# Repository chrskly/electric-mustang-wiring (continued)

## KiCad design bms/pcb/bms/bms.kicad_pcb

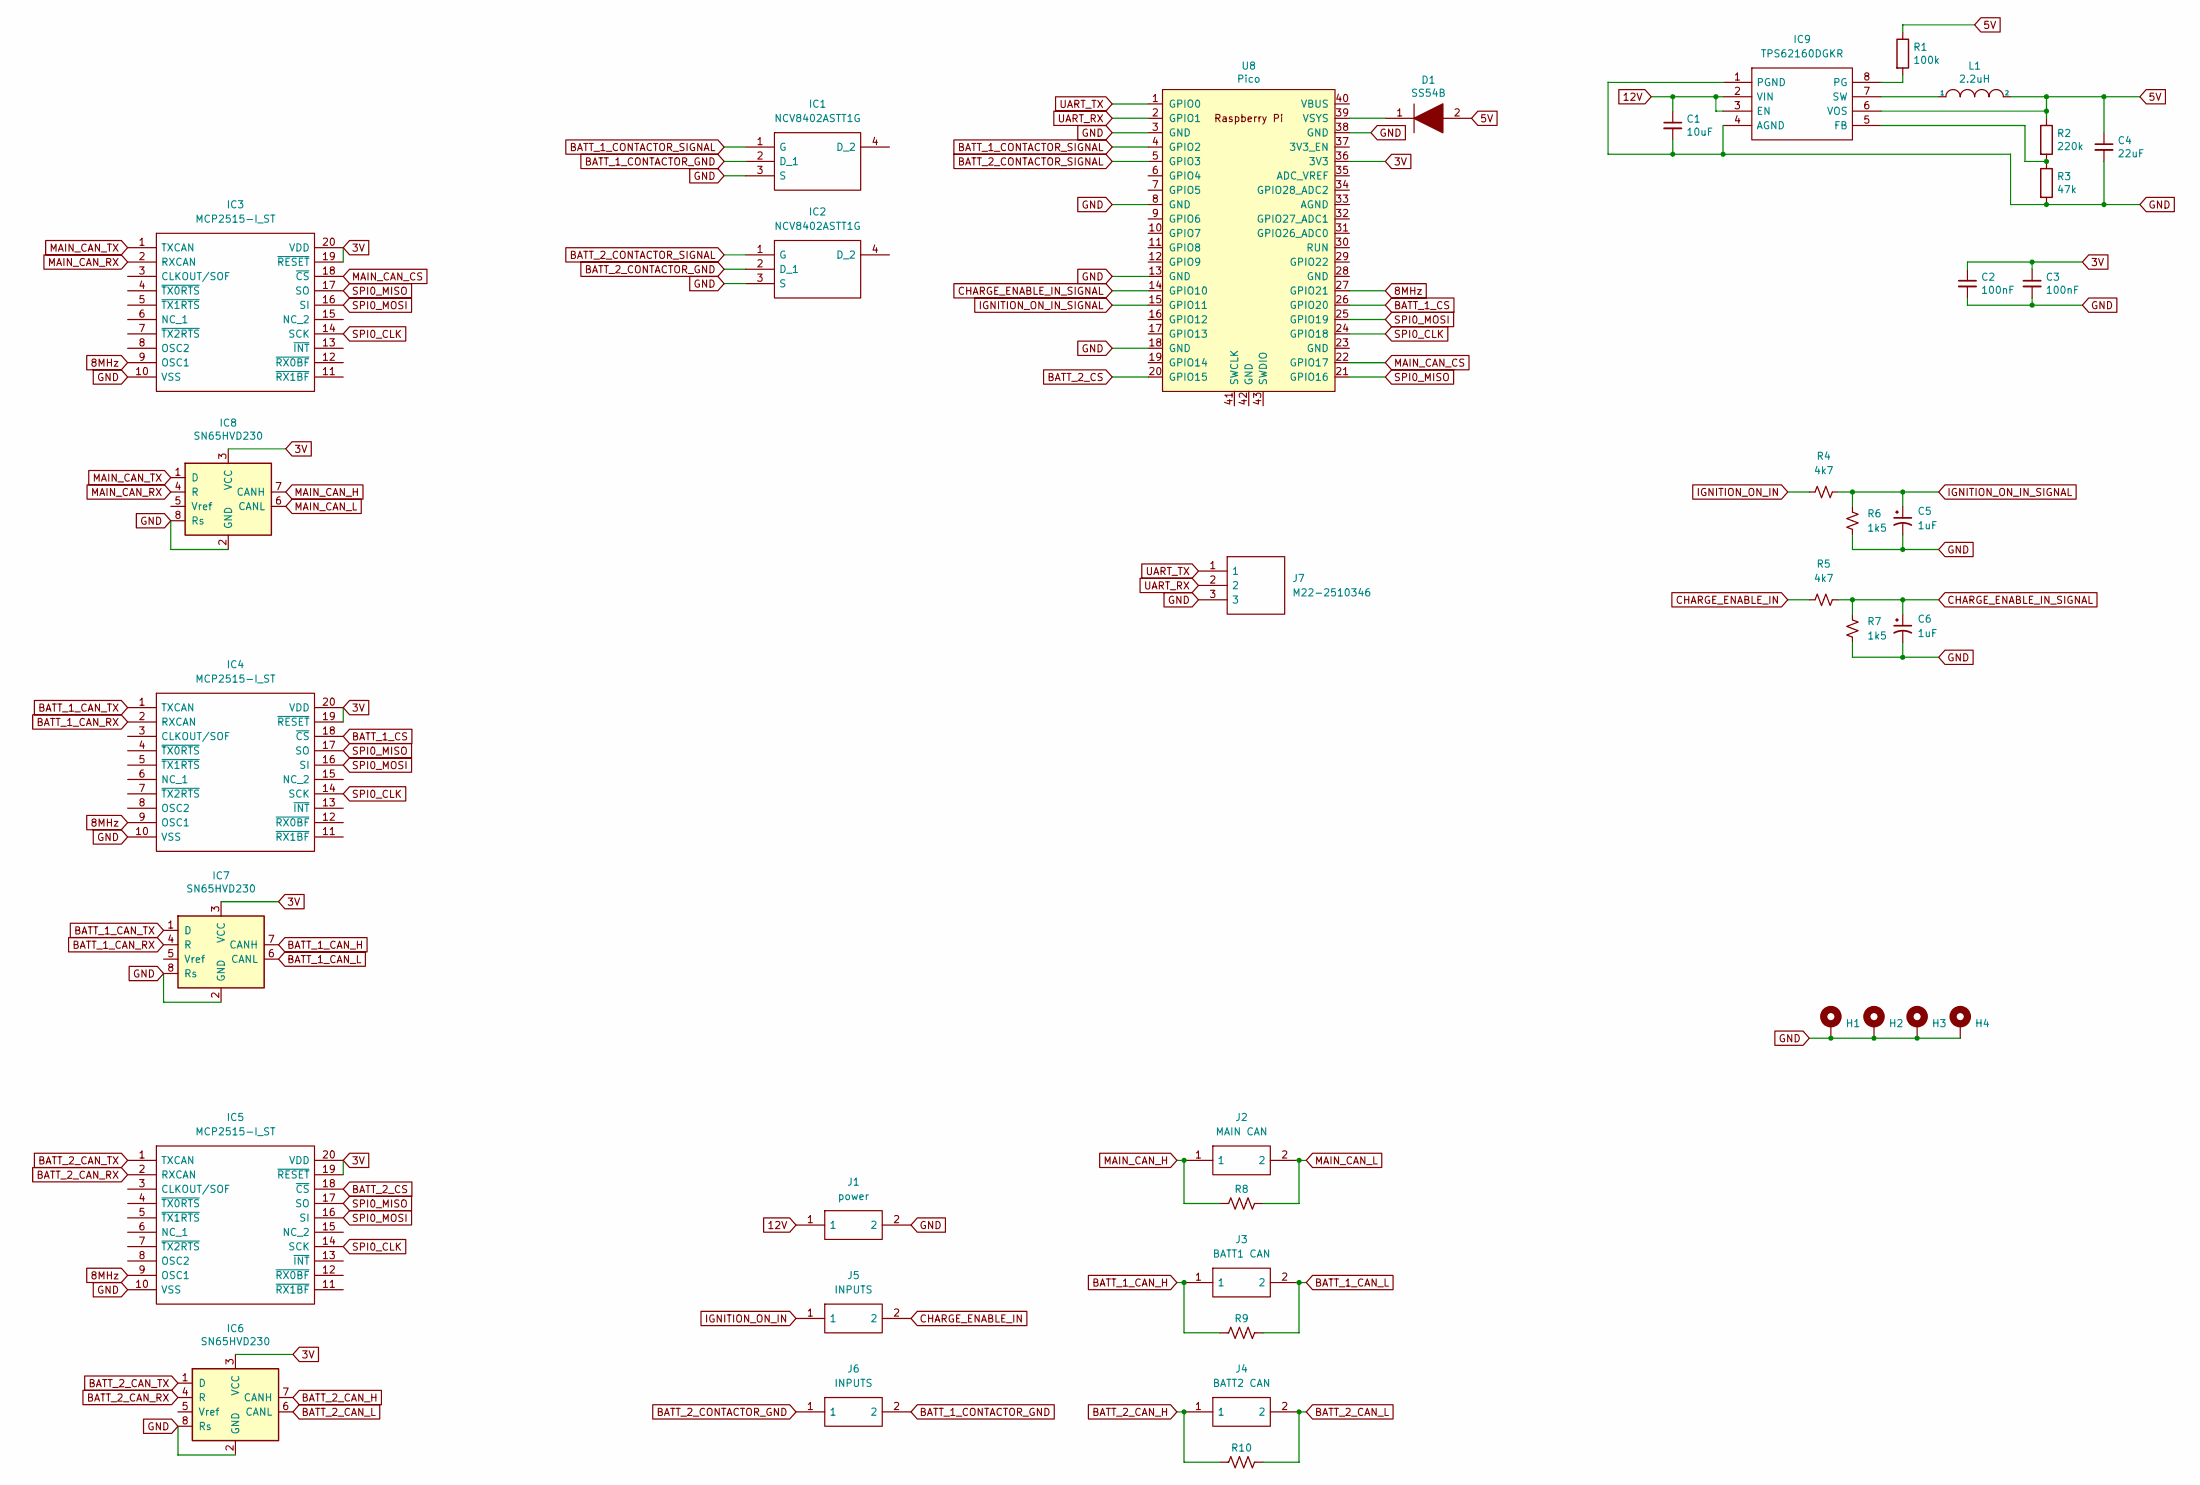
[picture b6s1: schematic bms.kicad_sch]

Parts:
C1: 10uF; C_0603_1608Metric
C2, C3: 100nF; C_0603_1608Metric
C4: 22uF; C_0805_2012Metric
C5, C6: 1uF; C_0603_1608Metric
D1: SS54B; DIOM5336X244N; Manufacturer_Part_Number SS54B
H1, H2, H3, H4: MountingHole; MountingHole_3.2mm_M3_Pad
IC1, IC2: NCV8402ASTT1G; SOT230P700X175-4N; Manufacturer_Part_Number NCV8402ASTT1G; Mouser Part Number 863-NCV8402ASTT1G
IC3, IC4, IC5: MCP2515-I_ST; SOP65P640X120-20N; Manufacturer_Part_Number MCP2515-I/ST
IC6, IC7, IC8: SN65HVD230; SOIC-8_3.9x4.9mm_P1.27mm
IC9: TPS62160DGKR; SOP65P490X110-8N; Manufacturer_Part_Number TPS62160DGKR; Mouser Part Number 595-TPS62160DGKR
J1: power; 105430YY02; Manufacturer_Part_Number 1054301102
J2: MAIN CAN; 105430YY02; Manufacturer_Part_Number 1054301102
J3: BATT1 CAN; 105430YY02; Manufacturer_Part_Number 1054301102
J4: BATT2 CAN; 105430YY02; Manufacturer_Part_Number 1054301102
J5, J6: INPUTS; 105430YY02; Manufacturer_Part_Number 1054301102
J7: M22-2510346; HDRV3W50P0X200_1X3_600X200X525P; Manufacturer_Part_Number M22-2510346; Mouser Part Number 855-M22-2510346
L1: 2.2uH; NR6028T220M
R1: 100k; R_0805_2012Metric
R2: 220k; R_0805_2012Metric
R3: 47k; R_0805_2012Metric
R4, R5: 4k7; R_0805_2012Metric
R6, R7: 1k5; R_0805_2012Metric
R8, R9, R10: 120; R_0805_2012Metric
U8: Pico; RPi_Pico_SMD_TH

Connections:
3V: C2.1, C3.1, IC3.19 (~RESET), IC3.20 (VDD), IC4.19 (~RESET), IC4.20 (VDD), IC5.19 (~RESET), IC5.20 (VDD), IC6.3 (VCC), IC7.3 (VCC), IC8.3 (VCC), U8.36 (3V3)
5V: C4.1, D1.2, IC9.6 (VOS), L1.2, R1.1, R2.1
8MHz: IC3.9 (OSC1), IC4.9 (OSC1), IC5.9 (OSC1), U8.27 (GPIO21)
12V: C1.1, IC9.2 (VIN), IC9.3 (EN), J1.1
BATT_1_CAN_H: IC7.7 (CANH), J3.1, R9.2
BATT_1_CAN_L: IC7.6 (CANL), J3.2, R9.1
BATT_1_CAN_RX: IC4.2 (RXCAN), IC7.4 (R)
BATT_1_CAN_TX: IC4.1 (TXCAN), IC7.1 (D)
BATT_1_CONTACTOR_GND: IC1.2 (D_1), J6.2
BATT_1_CONTACTOR_SIGNAL: IC1.1 (G), U8.4 (GPIO2)
BATT_1_CS: IC4.18 (~CS), U8.26 (GPIO20)
BATT_2_CAN_H: IC6.7 (CANH), J4.1, R10.2
BATT_2_CAN_L: IC6.6 (CANL), J4.2, R10.1
BATT_2_CAN_RX: IC5.2 (RXCAN), IC6.4 (R)
BATT_2_CAN_TX: IC5.1 (TXCAN), IC6.1 (D)
BATT_2_CONTACTOR_GND: IC2.2 (D_1), J6.1
BATT_2_CONTACTOR_SIGNAL: IC2.1 (G), U8.5 (GPIO3)
BATT_2_CS: IC5.18 (~CS), U8.20 (GPIO15)
CHARGE_ENABLE_IN: J5.2, R5.1
CHARGE_ENABLE_IN_SIGNAL: C6.1, R5.2, R7.1, U8.14 (GPIO10)
GND: C1.2, C2.2, C3.2, C4.2, C5.2, C6.2, H1.1, H2.1, H3.1, H4.1, IC1.3 (S), IC2.3 (S), IC3.10 (VSS), IC4.10 (VSS), IC5.10 (VSS), IC6.2 (GND), IC6.8 (Rs), IC7.2 (GND), IC7.8 (Rs), IC8.2 (GND), IC8.8 (Rs), IC9.1 (PGND), IC9.4 (AGND), J1.2, J7.3, R3.2, R6.2, R7.2, U8.3 (GND), U8.8 (GND), U8.13 (GND), U8.18 (GND), U8.38 (GND)
IGNITION_ON_IN: J5.1, R4.1
IGNITION_ON_IN_SIGNAL: C5.1, R4.2, R6.1, U8.15 (GPIO11)
MAIN_CAN_CS: IC3.18 (~CS), U8.22 (GPIO17)
MAIN_CAN_H: IC8.7 (CANH), J2.1, R8.2
MAIN_CAN_L: IC8.6 (CANL), J2.2, R8.1
MAIN_CAN_RX: IC3.2 (RXCAN), IC8.4 (R)
MAIN_CAN_TX: IC3.1 (TXCAN), IC8.1 (D)
unnamed: D1.1, U8.39 (VSYS)
unnamed: IC9.5 (FB), R2.2, R3.1
unnamed: IC9.7 (SW), L1.1
unnamed: IC9.8 (PG), R1.2
SPI0_CLK: IC3.14 (SCK), IC4.14 (SCK), IC5.14 (SCK), U8.24 (GPIO18)
SPI0_MISO: IC3.17 (SO), IC4.17 (SO), IC5.17 (SO), U8.21 (GPIO16)
SPI0_MOSI: IC3.16 (SI), IC4.16 (SI), IC5.16 (SI), U8.25 (GPIO19)
UART_RX: J7.2, U8.2 (GPIO1)
UART_TX: J7.1, U8.1 (GPIO0)

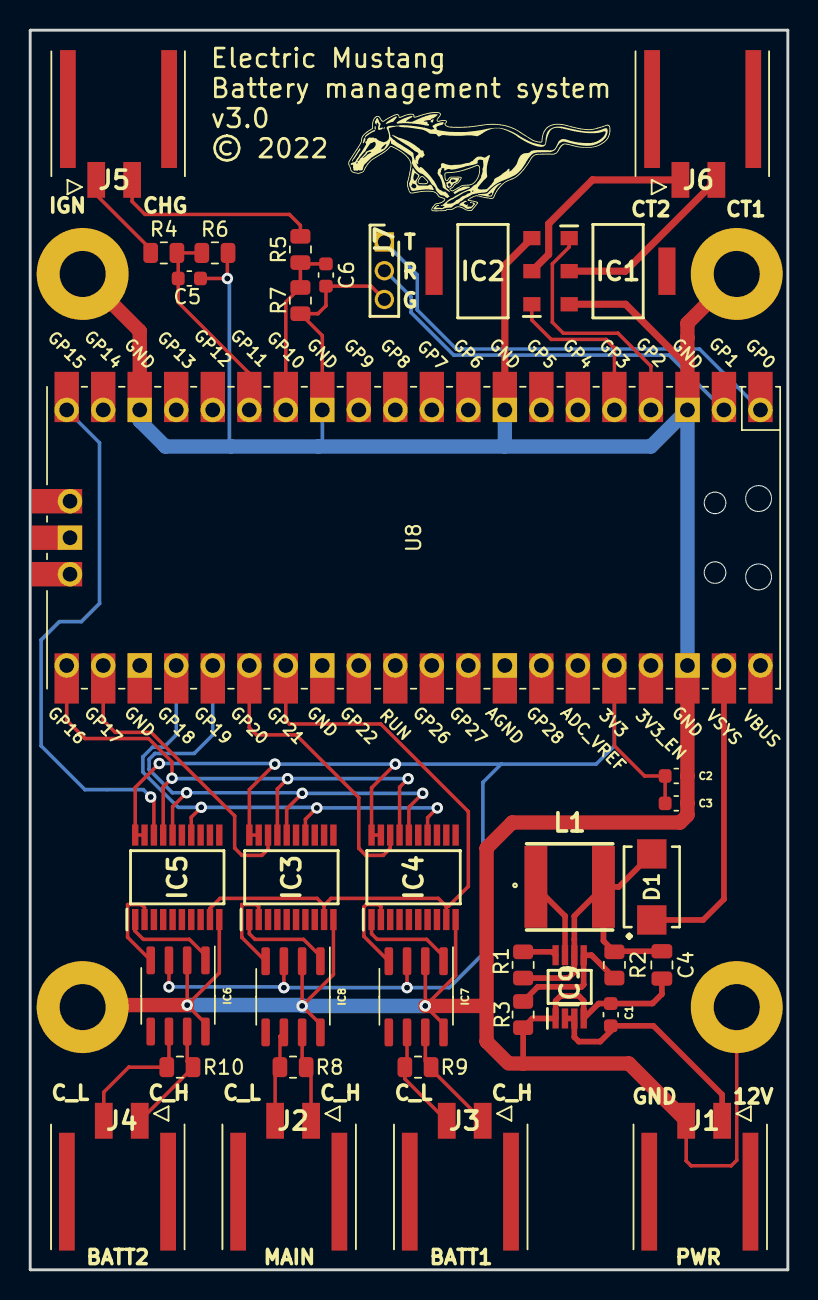
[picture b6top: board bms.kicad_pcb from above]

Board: 2 copper layers, 52.7 x 86.2 mm, 39 parts (0 on the bottom side), 37 nets.

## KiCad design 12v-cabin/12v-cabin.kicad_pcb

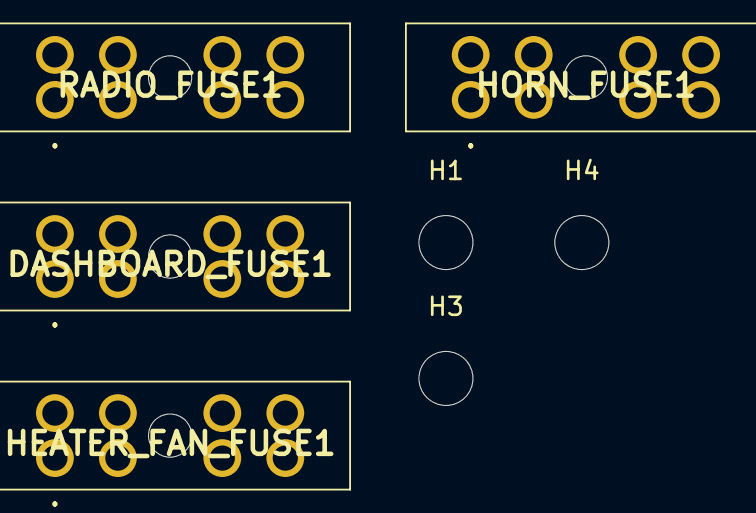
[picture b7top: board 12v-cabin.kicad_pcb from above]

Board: 2 copper layers, 8 parts (0 on the bottom side), 6 nets, no tracks yet.

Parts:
DASHBOARD_FUSE1: 178.6165.0001; 17861650001
H1, H2, H3, H4: MountingHole; MountingHole_3mm
HEATER_FAN_FUSE1: 178.6165.0001; 17861650001
HORN_FUSE1: 178.6165.0001; 17861650001
RADIO_FUSE1: 178.6165.0001; 17861650001

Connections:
DASHBOARD_12V: DASHBOARD_FUSE1.3, DASHBOARD_FUSE1.4, DASHBOARD_FUSE1.5, DASHBOARD_FUSE1.6
HEATER_FAN_12V: HEATER_FAN_FUSE1.3, HEATER_FAN_FUSE1.4, HEATER_FAN_FUSE1.5, HEATER_FAN_FUSE1.6
HORN_SWITCH_A: HEATER_FAN_FUSE1.1, HEATER_FAN_FUSE1.2, HEATER_FAN_FUSE1.7, HEATER_FAN_FUSE1.8, HORN_FUSE1.1, HORN_FUSE1.2, HORN_FUSE1.7, HORN_FUSE1.8
unnamed: HORN_FUSE1.3, HORN_FUSE1.4, HORN_FUSE1.5, HORN_FUSE1.6
unnamed: RADIO_FUSE1.3, RADIO_FUSE1.4, RADIO_FUSE1.5, RADIO_FUSE1.6
PERM_12V: DASHBOARD_FUSE1.1, DASHBOARD_FUSE1.2, DASHBOARD_FUSE1.7, DASHBOARD_FUSE1.8, RADIO_FUSE1.1, RADIO_FUSE1.2, RADIO_FUSE1.7, RADIO_FUSE1.8

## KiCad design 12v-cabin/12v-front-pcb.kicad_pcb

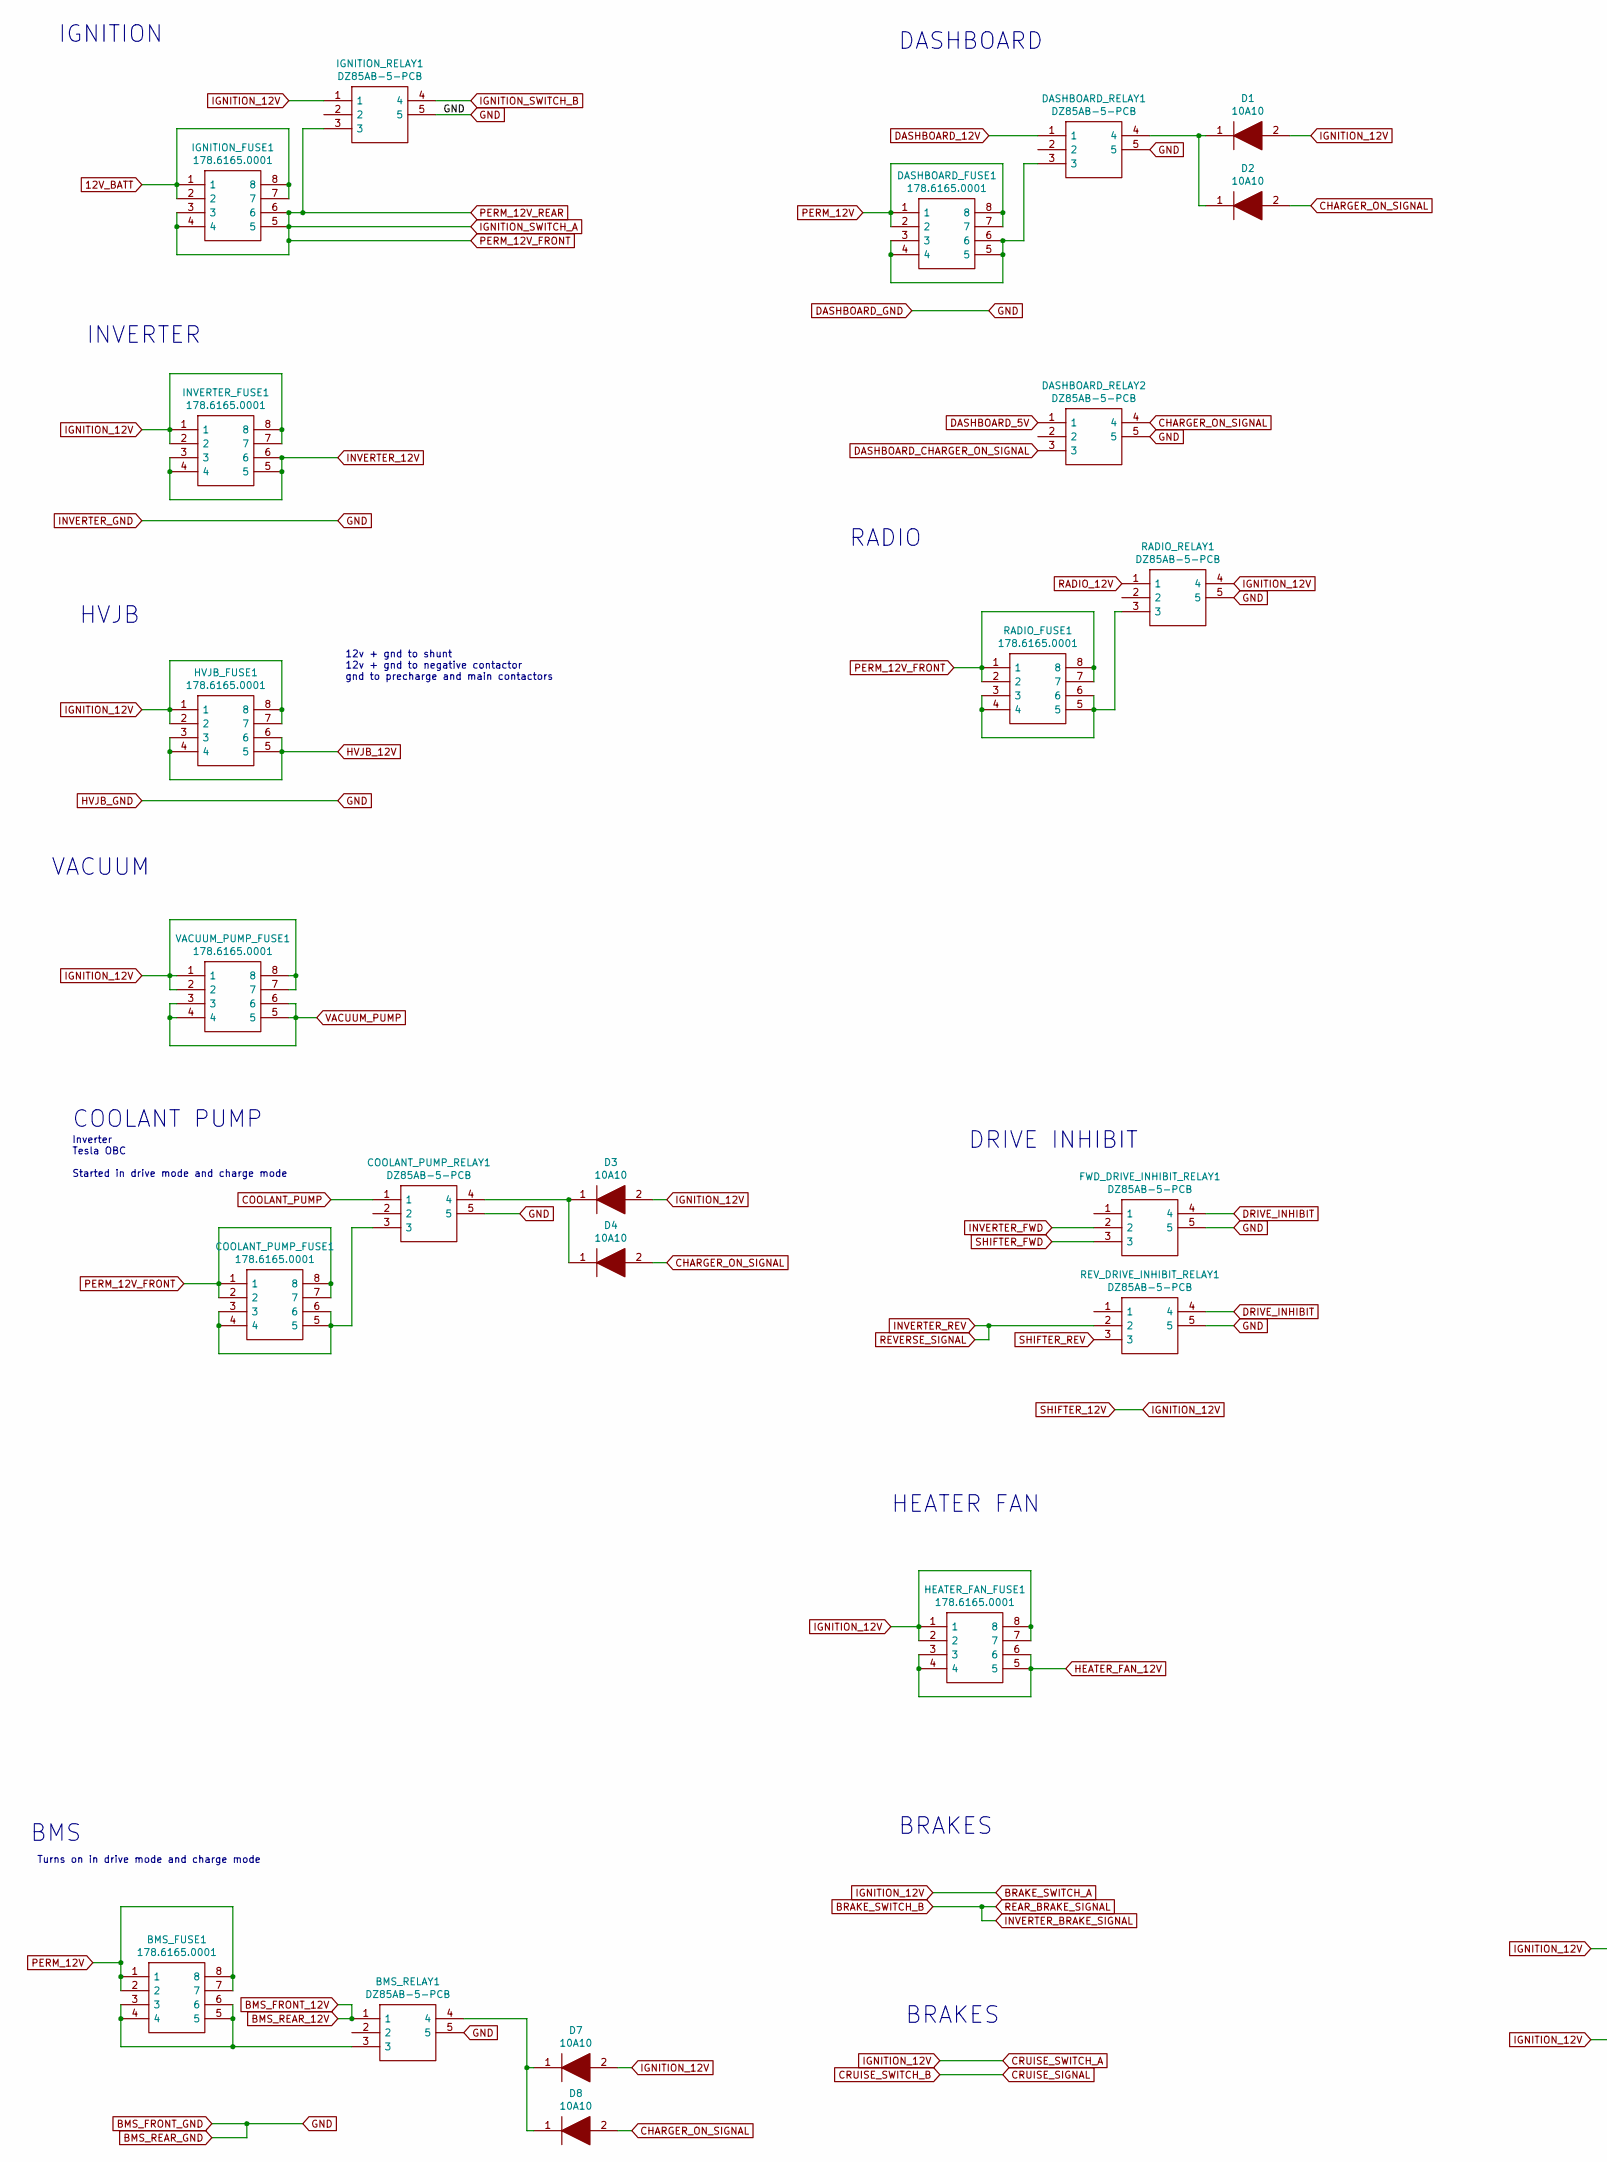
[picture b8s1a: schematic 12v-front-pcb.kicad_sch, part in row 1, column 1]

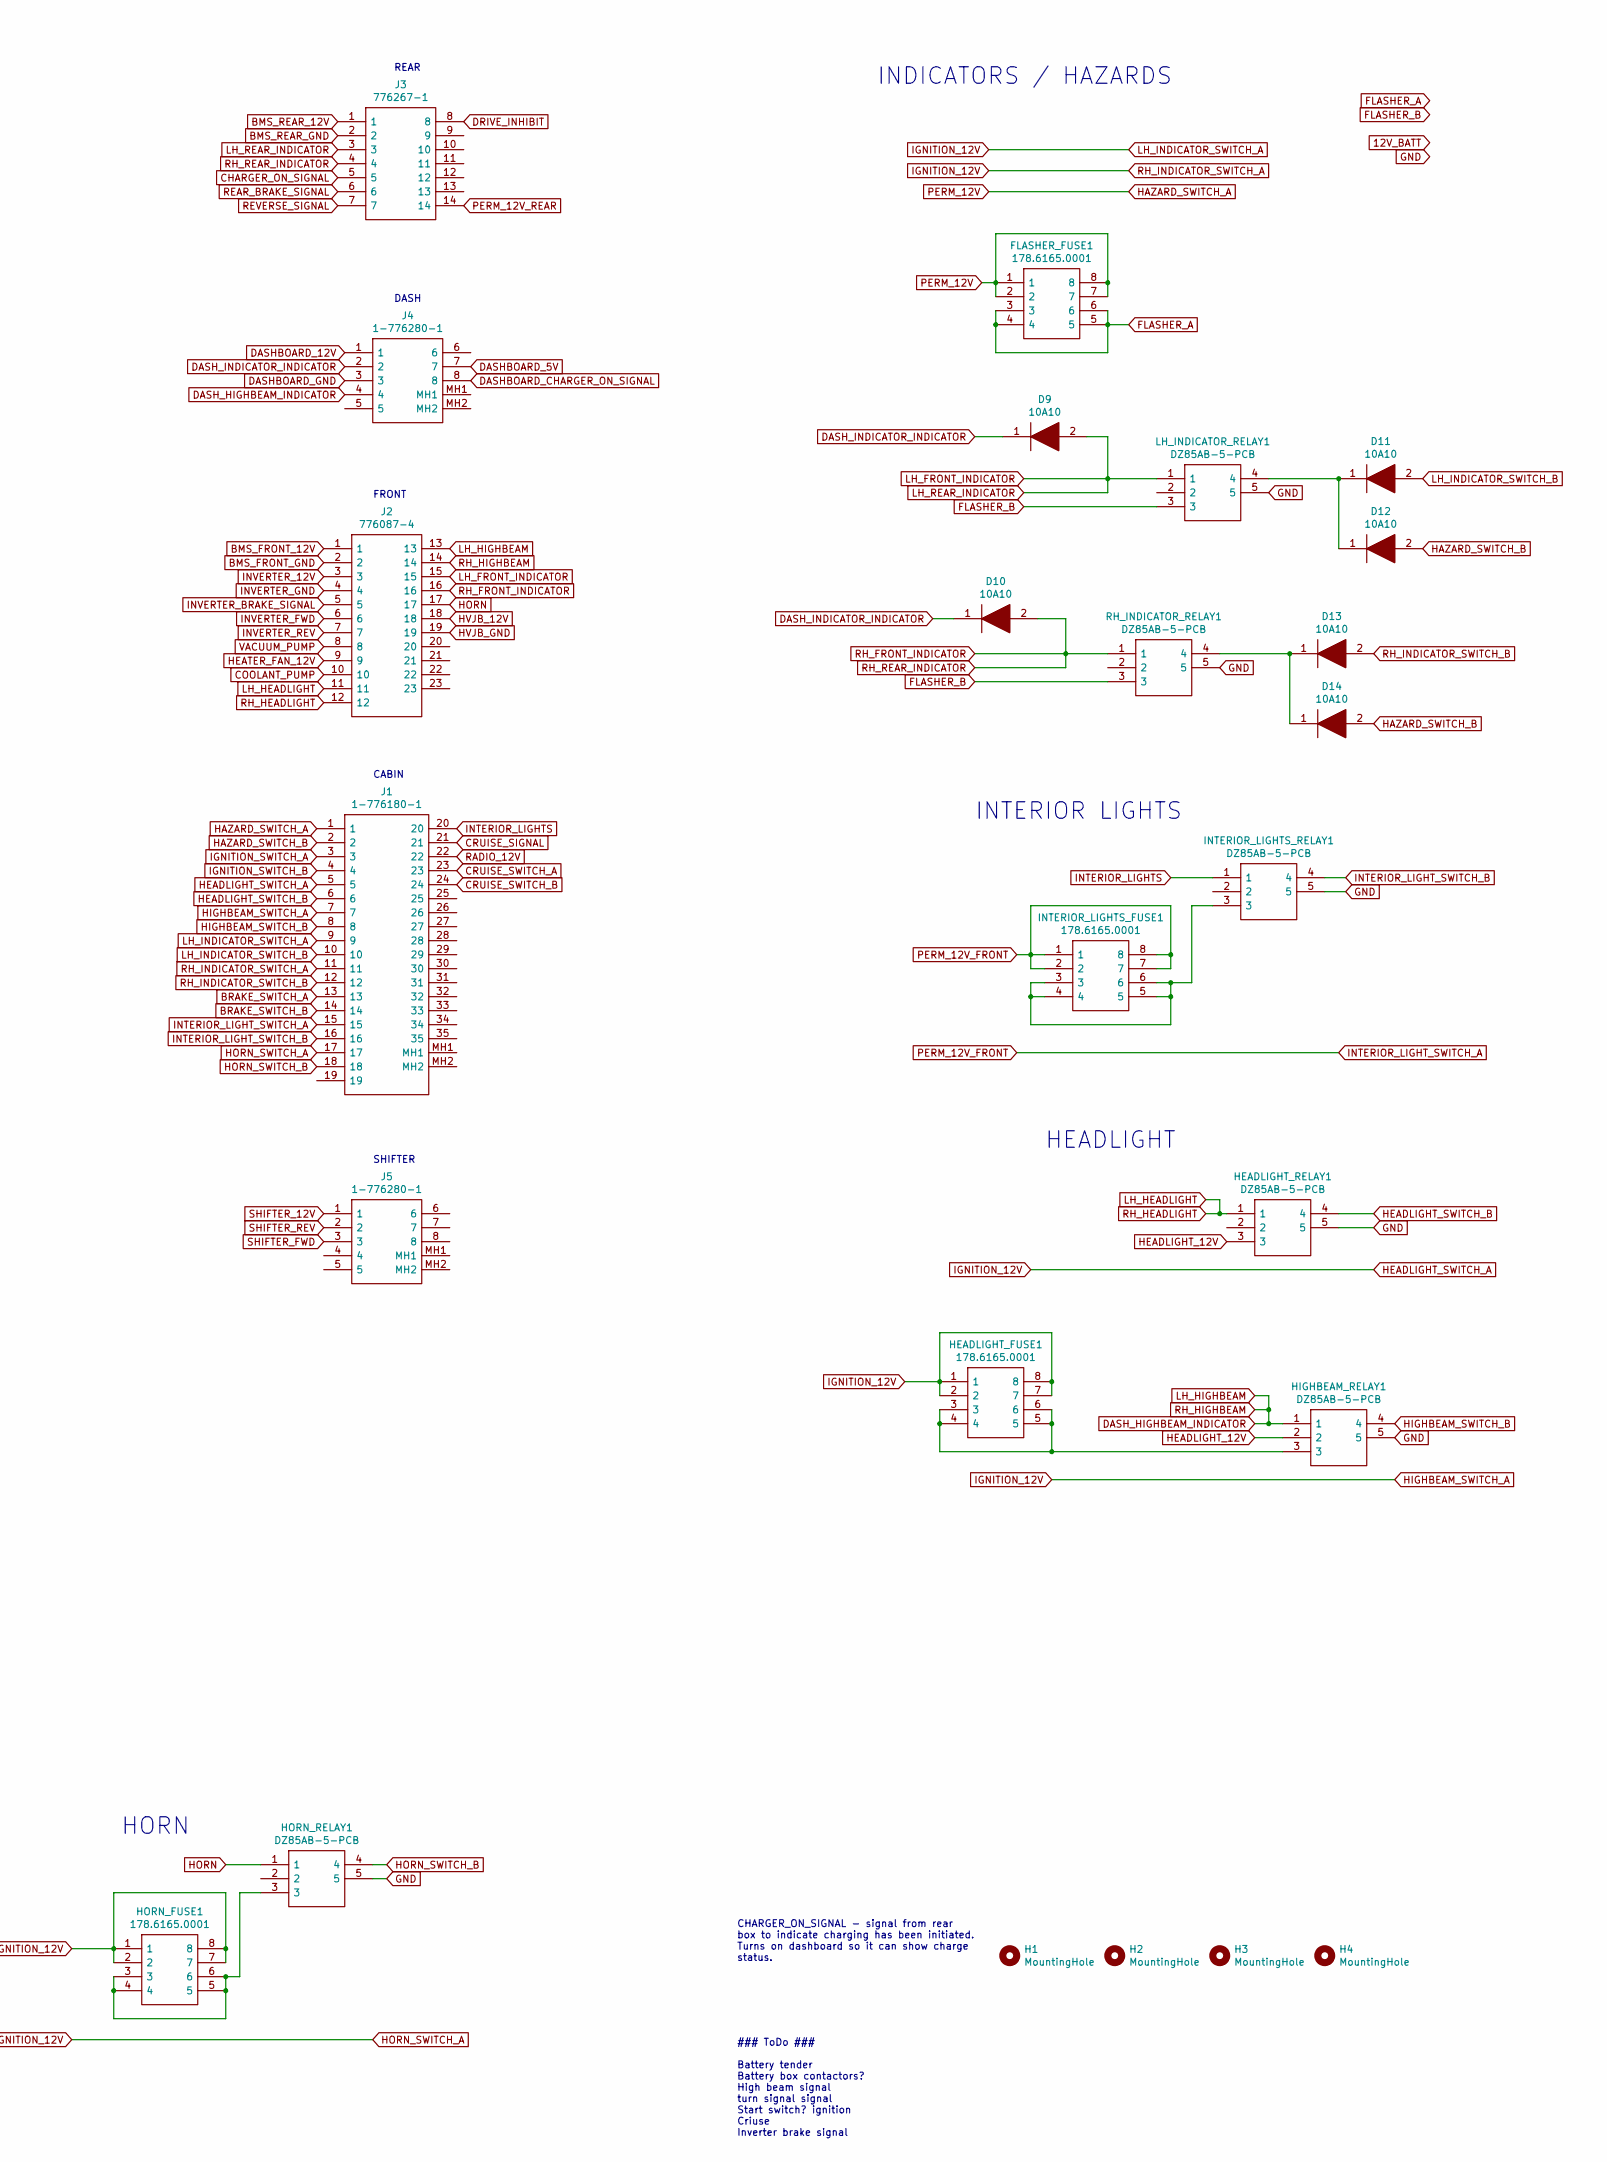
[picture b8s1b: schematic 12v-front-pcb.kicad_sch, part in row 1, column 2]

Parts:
BMS_FUSE1: 178.6165.0001; 17861650001; Manufacturer_Part_Number 178.6165.0001; Mouser Part Number 576-178.6165.0001
BMS_RELAY1: DZ85AB-5-PCB; DZ85AB5PCB; Manufacturer_Part_Number DZ85AB-5-PCB
COOLANT_PUMP_FUSE1: 178.6165.0001; 17861650001; Manufacturer_Part_Number 178.6165.0001; Mouser Part Number 576-178.6165.0001
COOLANT_PUMP_RELAY1: DZ85AB-5-PCB; DZ85AB5PCB; Manufacturer_Part_Number DZ85AB-5-PCB
D1, D2, D3, D4, D7, D8, D9, D10, D11, D12, D13, D14: 10A10; DIOAD1165W56L425D185; Manufacturer_Part_Number 10A10
DASHBOARD_FUSE1: 178.6165.0001; 17861650001; Manufacturer_Part_Number 178.6165.0001; Mouser Part Number 576-178.6165.0001
DASHBOARD_RELAY1, DASHBOARD_RELAY2: DZ85AB-5-PCB; DZ85AB5PCB; Manufacturer_Part_Number DZ85AB-5-PCB
FLASHER_FUSE1: 178.6165.0001; 17861650001; Manufacturer_Part_Number 178.6165.0001; Mouser Part Number 576-178.6165.0001
FWD_DRIVE_INHIBIT_RELAY1: DZ85AB-5-PCB; DZ85AB5PCB; Manufacturer_Part_Number DZ85AB-5-PCB
H1, H2, H3, H4: MountingHole; MountingHole_3mm
HEADLIGHT_FUSE1: 178.6165.0001; 17861650001; Manufacturer_Part_Number 178.6165.0001; Mouser Part Number 576-178.6165.0001
HEADLIGHT_RELAY1: DZ85AB-5-PCB; DZ85AB5PCB; Manufacturer_Part_Number DZ85AB-5-PCB
HEATER_FAN_FUSE1: 178.6165.0001; 17861650001; Manufacturer_Part_Number 178.6165.0001; Mouser Part Number 576-178.6165.0001
HIGHBEAM_RELAY1: DZ85AB-5-PCB; DZ85AB5PCB; Manufacturer_Part_Number DZ85AB-5-PCB
HORN_FUSE1: 178.6165.0001; 17861650001; Manufacturer_Part_Number 178.6165.0001; Mouser Part Number 576-178.6165.0001
HORN_RELAY1: DZ85AB-5-PCB; DZ85AB5PCB; Manufacturer_Part_Number DZ85AB-5-PCB
HVJB_FUSE1: 178.6165.0001; 17861650001; Manufacturer_Part_Number 178.6165.0001; Mouser Part Number 576-178.6165.0001
IGNITION_FUSE1: 178.6165.0001; 17861650001; Manufacturer_Part_Number 178.6165.0001; Mouser Part Number 576-178.6165.0001
IGNITION_RELAY1: DZ85AB-5-PCB; DZ85AB5PCB; Manufacturer_Part_Number DZ85AB-5-PCB
INTERIOR_LIGHTS_FUSE1: 178.6165.0001; 17861650001; Manufacturer_Part_Number 178.6165.0001; Mouser Part Number 576-178.6165.0001
INTERIOR_LIGHTS_RELAY1: DZ85AB-5-PCB; DZ85AB5PCB; Manufacturer_Part_Number DZ85AB-5-PCB
INVERTER_FUSE1: 178.6165.0001; 17861650001; Manufacturer_Part_Number 178.6165.0001; Mouser Part Number 576-178.6165.0001
J1: 1-776180-1; 17761801; Manufacturer_Part_Number 1-776180-1; Mouser Part Number 571-1-776180-1
J2: 776087-4; 7760874; Manufacturer_Part_Number 776087-4; Mouser Part Number 571-776087-4
J3: 776267-1; Manufacturer_Part_Number 776267-1; Mouser Part Number 571-776267-1
J4, J5: 1-776280-1; 17762801; Manufacturer_Part_Number 1-776280-1; Mouser Part Number 571-1-776280-1
LH_INDICATOR_RELAY1: DZ85AB-5-PCB; DZ85AB5PCB; Manufacturer_Part_Number DZ85AB-5-PCB
RADIO_FUSE1: 178.6165.0001; 17861650001; Manufacturer_Part_Number 178.6165.0001; Mouser Part Number 576-178.6165.0001
RADIO_RELAY1: DZ85AB-5-PCB; DZ85AB5PCB; Manufacturer_Part_Number DZ85AB-5-PCB
REV_DRIVE_INHIBIT_RELAY1: DZ85AB-5-PCB; DZ85AB5PCB; Manufacturer_Part_Number DZ85AB-5-PCB
RH_INDICATOR_RELAY1: DZ85AB-5-PCB; DZ85AB5PCB; Manufacturer_Part_Number DZ85AB-5-PCB
VACUUM_PUMP_FUSE1: 178.6165.0001; 17861650001; Manufacturer_Part_Number 178.6165.0001; Mouser Part Number 576-178.6165.0001

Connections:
12V_BATT: IGNITION_FUSE1.1, IGNITION_FUSE1.2, IGNITION_FUSE1.7, IGNITION_FUSE1.8
BMS_FRONT_12V: BMS_RELAY1.1, J2.1, J3.1
BMS_FRONT_GND: BMS_RELAY1.5, COOLANT_PUMP_RELAY1.5, DASHBOARD_RELAY1.5, DASHBOARD_RELAY2.5, FWD_DRIVE_INHIBIT_RELAY1.5, HEADLIGHT_RELAY1.5, HIGHBEAM_RELAY1.5, HORN_RELAY1.5, IGNITION_RELAY1.5, INTERIOR_LIGHTS_RELAY1.5, J2.2, J2.4, J2.19, J3.2, J4.3, LH_INDICATOR_RELAY1.5, RADIO_RELAY1.5, REV_DRIVE_INHIBIT_RELAY1.5, RH_INDICATOR_RELAY1.5; also elsewhere on the board
BRAKE_SWITCH_A: D1.2, D3.2, D7.2, HEADLIGHT_FUSE1.1, HEADLIGHT_FUSE1.2, HEADLIGHT_FUSE1.7, HEADLIGHT_FUSE1.8, HEATER_FAN_FUSE1.1, HEATER_FAN_FUSE1.2, HEATER_FAN_FUSE1.7, HEATER_FAN_FUSE1.8, HORN_FUSE1.1, HORN_FUSE1.2, HORN_FUSE1.7, HORN_FUSE1.8, HVJB_FUSE1.1, HVJB_FUSE1.2, HVJB_FUSE1.7, HVJB_FUSE1.8, IGNITION_RELAY1.1, INVERTER_FUSE1.1, INVERTER_FUSE1.2, INVERTER_FUSE1.7, INVERTER_FUSE1.8, J1.5, J1.7, J1.9, J1.11, J1.13, J1.17, J1.23, J5.1, RADIO_RELAY1.4, VACUUM_PUMP_FUSE1.1, VACUUM_PUMP_FUSE1.2, VACUUM_PUMP_FUSE1.7, VACUUM_PUMP_FUSE1.8
BRAKE_SWITCH_B: J1.14, J2.5, J3.6
CHARGER_ON_SIGNAL: D2.2, D4.2, D8.2, DASHBOARD_RELAY2.4, J3.5
COOLANT_PUMP: COOLANT_PUMP_RELAY1.1, J2.10
CRUISE_SIGNAL: J1.21, J1.24
DASHBOARD_5V: DASHBOARD_RELAY2.1, J4.7
DASHBOARD_12V: DASHBOARD_RELAY1.1, J4.1
DASHBOARD_CHARGER_ON_SIGNAL: DASHBOARD_RELAY2.3, J4.8
DASH_HIGHBEAM_INDICATOR: HIGHBEAM_RELAY1.1, J2.13, J2.14, J4.4
DASH_INDICATOR_INDICATOR: D9.1, D10.1, J4.2
DRIVE_INHIBIT: FWD_DRIVE_INHIBIT_RELAY1.4, J3.8, REV_DRIVE_INHIBIT_RELAY1.4
FLASHER_A: FLASHER_FUSE1.3, FLASHER_FUSE1.4, FLASHER_FUSE1.5, FLASHER_FUSE1.6
FLASHER_B: LH_INDICATOR_RELAY1.3, RH_INDICATOR_RELAY1.3; also elsewhere on the board
HAZARD_SWITCH_A: BMS_FUSE1.1, BMS_FUSE1.2, BMS_FUSE1.7, BMS_FUSE1.8, DASHBOARD_FUSE1.1, DASHBOARD_FUSE1.2, DASHBOARD_FUSE1.7, DASHBOARD_FUSE1.8, FLASHER_FUSE1.1, FLASHER_FUSE1.2, FLASHER_FUSE1.7, FLASHER_FUSE1.8, J1.1
HAZARD_SWITCH_B: D12.2, D14.2, J1.2
HEADLIGHT_12V: HEADLIGHT_RELAY1.3, HIGHBEAM_RELAY1.2
HEADLIGHT_SWITCH_B: HEADLIGHT_RELAY1.4, J1.6
HEATER_FAN_12V: HEATER_FAN_FUSE1.3, HEATER_FAN_FUSE1.4, HEATER_FAN_FUSE1.5, HEATER_FAN_FUSE1.6, J2.9
HIGHBEAM_SWITCH_B: HIGHBEAM_RELAY1.4, J1.8
HORN: HORN_RELAY1.1, J2.17
HORN_SWITCH_B: HORN_RELAY1.4, J1.18
HVJB_12V: HVJB_FUSE1.3, HVJB_FUSE1.4, HVJB_FUSE1.5, HVJB_FUSE1.6, J2.18
IGNITION_SWITCH_A: COOLANT_PUMP_FUSE1.1, COOLANT_PUMP_FUSE1.2, COOLANT_PUMP_FUSE1.7, COOLANT_PUMP_FUSE1.8, IGNITION_FUSE1.3, IGNITION_FUSE1.4, IGNITION_FUSE1.5, IGNITION_FUSE1.6, IGNITION_RELAY1.3, INTERIOR_LIGHTS_FUSE1.1, INTERIOR_LIGHTS_FUSE1.2, INTERIOR_LIGHTS_FUSE1.7, INTERIOR_LIGHTS_FUSE1.8, J1.3, J1.15, J3.14, RADIO_FUSE1.1, RADIO_FUSE1.2, RADIO_FUSE1.7, RADIO_FUSE1.8
IGNITION_SWITCH_B: IGNITION_RELAY1.4, J1.4
INTERIOR_LIGHTS: INTERIOR_LIGHTS_RELAY1.1, J1.20
INTERIOR_LIGHT_SWITCH_B: INTERIOR_LIGHTS_RELAY1.4, J1.16
INVERTER_12V: INVERTER_FUSE1.3, INVERTER_FUSE1.4, INVERTER_FUSE1.5, INVERTER_FUSE1.6, J2.3
INVERTER_FWD: FWD_DRIVE_INHIBIT_RELAY1.2, J2.6
INVERTER_REV: J2.7, J3.7, REV_DRIVE_INHIBIT_RELAY1.2
LH_FRONT_INDICATOR: D9.2, J2.15, J3.3, LH_INDICATOR_RELAY1.1
LH_HEADLIGHT: HEADLIGHT_RELAY1.1, J2.11, J2.12
LH_INDICATOR_SWITCH_B: D11.2, J1.10
unnamed: BMS_FUSE1.3, BMS_FUSE1.4, BMS_FUSE1.5, BMS_FUSE1.6, BMS_RELAY1.3
unnamed: BMS_RELAY1.4, D7.1, D8.1
unnamed: COOLANT_PUMP_FUSE1.3, COOLANT_PUMP_FUSE1.4, COOLANT_PUMP_FUSE1.5, COOLANT_PUMP_FUSE1.6, COOLANT_PUMP_RELAY1.3
unnamed: COOLANT_PUMP_RELAY1.4, D3.1, D4.1
unnamed: D1.1, D2.1, DASHBOARD_RELAY1.4
unnamed: D11.1, D12.1, LH_INDICATOR_RELAY1.4
unnamed 43: D13.1, D14.1, RH_INDICATOR_RELAY1.4; also elsewhere on the board
unnamed: DASHBOARD_FUSE1.3, DASHBOARD_FUSE1.4, DASHBOARD_FUSE1.5, DASHBOARD_FUSE1.6, DASHBOARD_RELAY1.3
unnamed: HEADLIGHT_FUSE1.3, HEADLIGHT_FUSE1.4, HEADLIGHT_FUSE1.5, HEADLIGHT_FUSE1.6, HIGHBEAM_RELAY1.3
unnamed: HORN_FUSE1.3, HORN_FUSE1.4, HORN_FUSE1.5, HORN_FUSE1.6, HORN_RELAY1.3
unnamed: INTERIOR_LIGHTS_FUSE1.3, INTERIOR_LIGHTS_FUSE1.4, INTERIOR_LIGHTS_FUSE1.5, INTERIOR_LIGHTS_FUSE1.6, INTERIOR_LIGHTS_RELAY1.3
unnamed: RADIO_FUSE1.3, RADIO_FUSE1.4, RADIO_FUSE1.5, RADIO_FUSE1.6, RADIO_RELAY1.3
RADIO_12V: J1.22, RADIO_RELAY1.1
RH_FRONT_INDICATOR: D10.2, J2.16, J3.4, RH_INDICATOR_RELAY1.1; also elsewhere on the board
RH_INDICATOR_SWITCH_B: D13.2, J1.12
SHIFTER_FWD: FWD_DRIVE_INHIBIT_RELAY1.3, J5.3
SHIFTER_REV: J5.2, REV_DRIVE_INHIBIT_RELAY1.3
VACUUM_PUMP: J2.8, VACUUM_PUMP_FUSE1.3, VACUUM_PUMP_FUSE1.4, VACUUM_PUMP_FUSE1.5, VACUUM_PUMP_FUSE1.6

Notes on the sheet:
IGNITION
DASHBOARD
### ToDo ### Battery tender Battery box contactors? High beam signal turn signal signal Start switch? ignition Criuse Inverter brake signal
Inverter Tesla OBC Started in drive mode and charge mode
12v + gnd to shunt 12v + gnd to negative contactor gnd to precharge and main contactors
SHIFTER
HORN
FRONT
RADIO
BRAKES
HEADLIGHT
HVJB
INTERIOR LIGHTS
VACUUM
INDICATORS / HAZARDS
INVERTER
BMS
CHARGER_ON_SIGNAL - signal from rear box to indicate charging has been initiated. Turns on dashboard so it can show charge status.
COOLANT PUMP
HEATER FAN
REAR
DRIVE INHIBIT
DASH
Turns on in drive mode and charge mode
CABIN

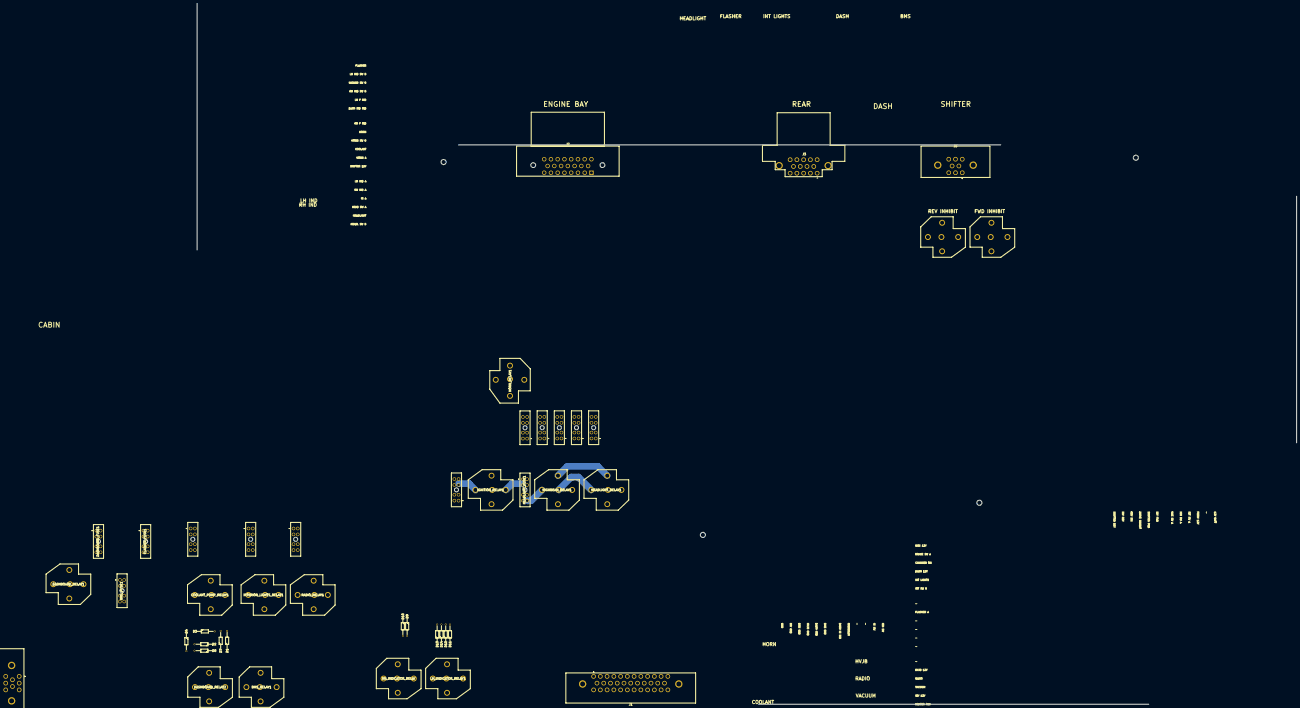
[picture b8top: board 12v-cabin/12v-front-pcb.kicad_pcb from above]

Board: 2 copper layers, 651.5 x 415.3 mm, 48 parts (0 on the bottom side), 53 nets.

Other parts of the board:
RH_INDICATOR_RELAY: DZ85AB-5-PCB; DZ85AB5PCB

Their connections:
BMS_FRONT_GND: RH_INDICATOR_RELAY.5; also elsewhere on the board
FLASHER_B: RH_INDICATOR_RELAY.3; also elsewhere on the board
unnamed 43: RH_INDICATOR_RELAY.4; also elsewhere on the board
RH_FRONT_INDICATOR: RH_INDICATOR_RELAY.1; also elsewhere on the board

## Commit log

2021-11-30 Add gitignore
2021-11-30 Add front schematic/pcb
2021-11-30 Add rear pcb
2021-12-04 Add dash vcu
2021-12-04 docs
2021-12-05 dash tweaks
2021-12-05 Initial testing of driving fuel gauge with pwm and a TIP101
2021-12-05 README
2021-12-05 Add TODO
2021-12-05 syntax
2021-12-05 mystery bad whitespace
2021-12-08 Tweaks
2022-01-07 Split out lighting fuses/relays to separate board
2022-01-08 Re-work front PCB
2022-01-08 Switch to using Pi Pico for dash vcu
2022-05-12 Start working on functional spec for bms, charge controller, and dashboaord
2022-05-14 Begin work on functional specs
2022-05-18 Add 12v inventory
2022-05-18 Notes for pico programming
2022-05-18 gitignore
2022-05-18 more gitignore
2022-05-18 Add beginnging of BMS code
2022-05-18 12v cabin board
2022-05-18 12v lighting
2022-05-18 12v front board
2022-05-18 12v rear
2022-05-18 Functional spec for BMS
2022-05-18 Add functional spec for charge controller
2022-05-18 wiring diagrams
2022-05-18 dashboard functional spec
2022-05-18 some dashboard
2022-05-23 starting to put some shape on the bms code
2022-05-24 Various bits of reorganising
2022-05-28 Add beginning of BMS circuit.
2022-05-31 v1.0 of BMS finalised. Sent of for fabrication
2022-06-03 Finalised 12v front PCB design (engine board) and sent for fabrication
2022-06-03 Add 12v-front to wiring diagrams
2022-06-04 Syntax fix
2022-06-04 slight tweaks to bms functional spec
2022-06-04 Tidy README.md
2022-06-07 roughing out various bits of the bms
2022-06-10 Add licence
2022-06-10 Basic contactor control
2022-06-11 work on state machine transitions
2022-06-12 Work on reading voltage and temperature readings
2022-06-12 Don't need these
2022-06-13 little cleaning
2022-06-13 BMS PCB fixes. Serial header for debugging. Heavier traces in certain places. Fix some pico pin connections.
2022-06-13 just some 12v-front backups from having it open
2022-06-14 Working on asking for and decoding data
2022-06-14 Send out poll messages to all packs automatically
2022-06-14 Cleanup cabin pcb
2022-06-16 underscores over camelCase
2022-06-16 comments update
2022-06-16 Tweak function name
2022-06-16 fix fn name
2022-06-29 Redo gerbers
2022-06-29 v2 of bms sent off for fabrication
2022-07-11 Fix up initialisation of variables and try getting pack polling to work
2022-07-11 Found two more errors in bms. Create version 3
2022-07-18 Feck it. Re-work it to an object-oriented structure
2022-07-29 Fix setup of CAN ports
2022-07-30 Various restructuring. Now sending and receiving CAN messages. Added LED flashing.
2022-07-30 Rework front PCB to make more room for relays
2022-07-30 Small tidy
2022-07-30 tidy backups
2022-12-05 Split wiring diagrams into individual files to make things more readable
2022-12-05 split up CCS_HVJB contactors to individual devices
2022-12-05 reorg
2022-12-05 Split out charge contactors
2023-01-02 BMS pcb v4
2023-01-07 12v front backups
2023-01-07 12v lighting backups
2023-01-07 12v rear backups
2023-01-07 dashboard vcu backups
2023-01-07 bms backups
2023-01-07 BMS successfully fetching voltage and temperature data
2023-01-07 add some sample messages from simp
2023-01-07 Playing around with simulating sounds
2023-01-07 Add lighting wiring diagrams
2023-01-07 Updates to the 12v front pcb
2023-01-07 gerbers for v4 pcb
2023-01-07 whitespace
2023-01-12 Work on BMS state machine
2023-01-15 various bits of fixing and cleanup
2023-01-15 Whitespace. Unused variables. contactor control little cleanup
2023-01-15 Get status light working as intended. Different flash patterns for standby, drive, charge, and fault
2023-01-15 remove some debugging
2023-01-15 functional spec update
2023-01-17 working on pcb for tail lights
2023-01-19 Get cell delta working. Fix module id off-by-one.
2023-01-20 Set up output pins
2023-01-21 Add inputs for CHARGE_ENABLE and IGNITION_ON. Deal with charge termination. Add logging to state transitions. Change status light mode properly.
2023-01-22 store cellDelta in mV. Simplify status print.
2023-01-22 Adjust status print
2023-01-22 12v-front backups
2023-01-22 bms pcb backups
2023-01-22 .gitignore update
2023-01-22 pcb backup
2023-01-22 Dashboard vcu update
2023-03-11 brake pedal, cruise button, new BMS pinout
2023-03-14 BMS updates to functional spec
2023-03-16 Finalise tail-lights. Send off for fab
2023-03-16 Errors in charge/drive mode
2023-03-18 lighting board. Add reverse light. Fix up a couple of issues.
2023-03-18 Fixing issues on 12-front. lots of updates to wiring diagrams
2023-03-18 minor tweaks
2023-03-18 backups
2023-03-20 start outlining charge controller code
2023-03-23 Set up build environment. Add other CAN bus interfaces. Listen for IN1/IN2 signals (chademo). Handle inbound ChaDeMo CAN frames.
2023-03-23 Add watchdog to bms
2023-03-25 Moving things around
2023-03-26 Begin work on tail-light code
2023-03-26 Deal with some of the CAN communications
2023-04-07 The states on the EVSE side don't map cleanly to car-side states. So, just make up some car-side states. WIP
2023-04-09 Read msgs from ISA shunt. Send (some) SimpBMS format status messages.
2023-04-09 random updates
2023-04-09 kicad backups
2023-04-09 Make charger build before going further
2023-04-09 Fix references
2023-04-09 reorg externs
2023-04-10 Various reorg bits
2023-04-13 Working on chademo state machine
2023-04-14 Fiddling around
2023-04-15 Add current ramping to chademo and read messages from BMS
2023-04-16 Calculate SoC. Reset ISA shunt after charging to 100%
2023-04-16 Send amps in status message
2023-04-17 Work a bit on charge_inhibit for chademo
2023-04-22 Add separate error states for overTemp, illegalStateTransition
2023-04-22 simplify
2023-04-22 ah/kw mixed up
2023-04-27 Restructuring a bit
2023-04-27 Fix msg formatting
2023-04-27 little clean up
2023-04-28 fix vehicle status reporting
2023-04-30 Deal with CC/CV charging phases. refactor some error handling
2023-04-30 Transmit measured voltage as part of BMS messages
2023-05-01 Deal with CC/CV windows. Deal with charge termination
2023-05-01 More debug msgs + some minor fixes
2023-05-02 Fix state change
2023-05-02 Catch some error conditions
2023-05-02 stopContol should be used in this way
2023-05-07 Missing scaling factor
2023-05-07 logic inverted
2023-05-13 more info for invalid events
2023-12-05 Start writing test cases for BMS
2023-12-09 pcb backups
2023-12-09 rework on 12v front pcb
2023-12-09 Work BMS test cases
2024-01-25 Send tail lights v2 for fabrication
2024-02-20 cpplint recommendations and some other cleanup
2024-02-29 Move bms code over to separate repo
2024-02-29 some tail light stuff
